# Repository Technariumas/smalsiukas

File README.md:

# smalsiukas
The conversion of a forklift trucks to a line following robot. 

A file set related to conversion of BT C3E C4E forklift truck and Linde lifter to a line-following robot for an art installation of [Robertas Narkus "Träger"](http://cac.lt/en/exhibitions/future/8547)

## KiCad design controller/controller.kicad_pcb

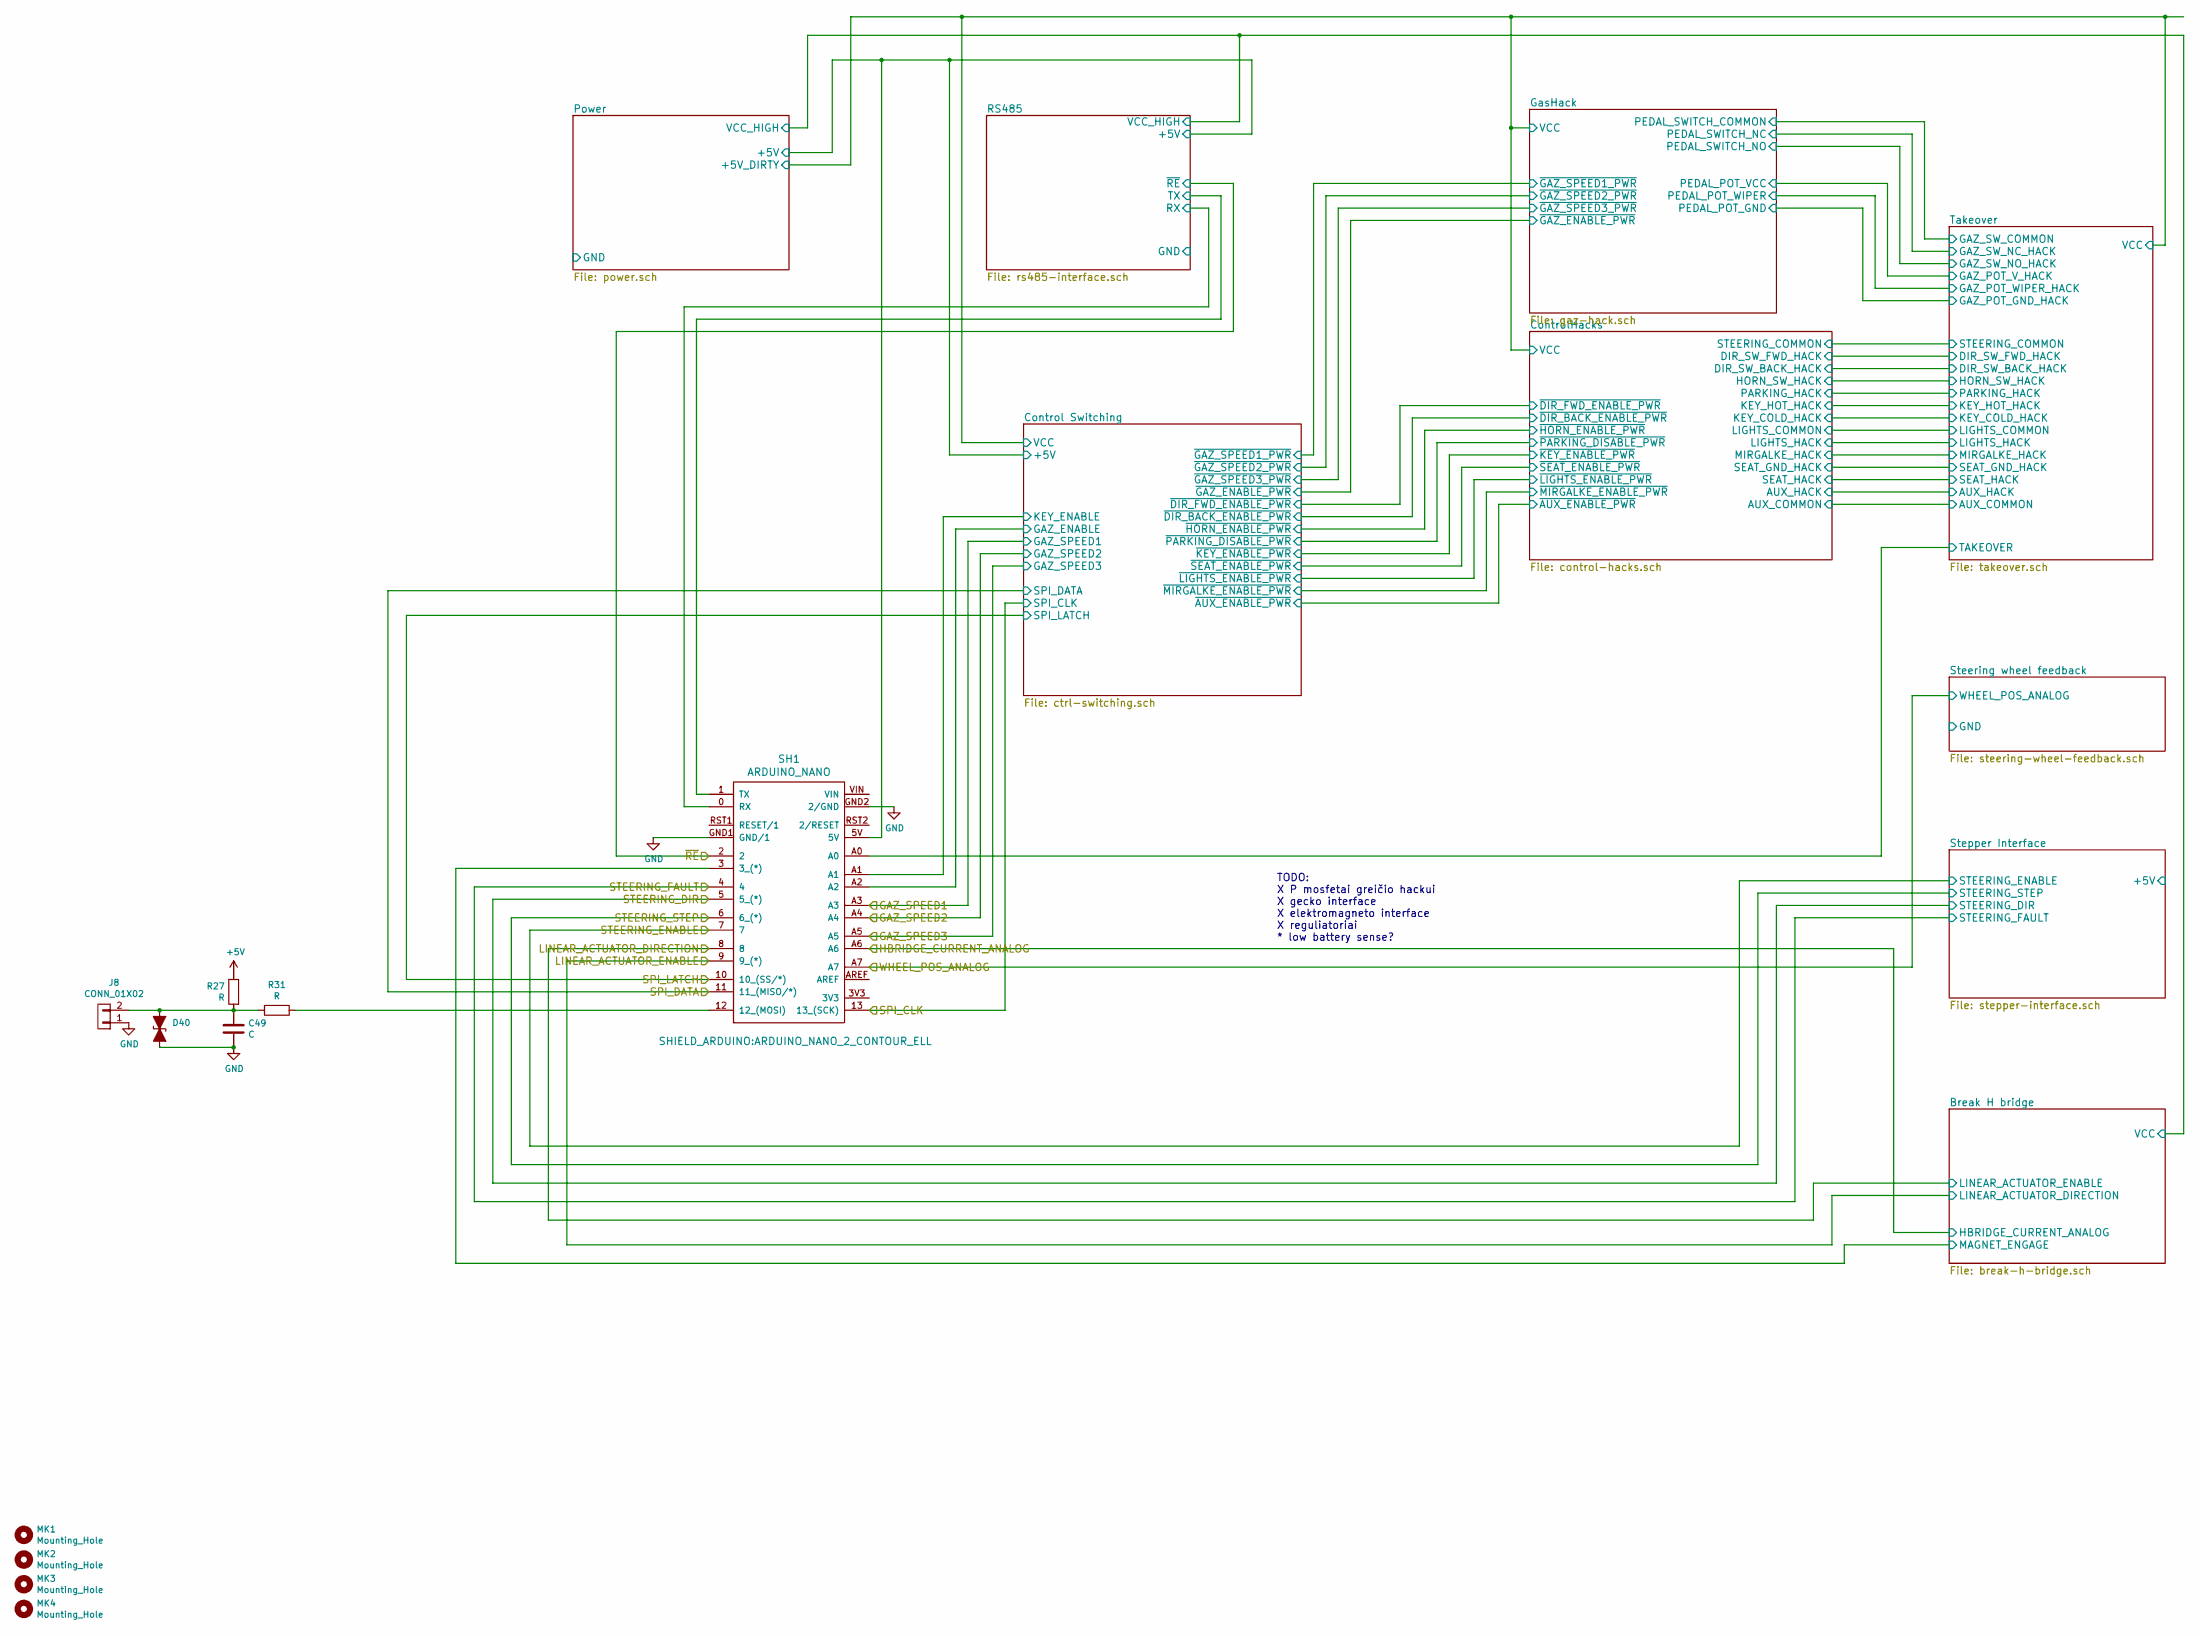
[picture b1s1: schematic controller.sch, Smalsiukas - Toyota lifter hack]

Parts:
C49: C; C_0603_HandSoldering; PartNo ?
D40: D_TVS_ALT; SOD-323; PartNo ?
J8: CONN_01X02; JST_EH_B02B-EH-A_02x2.50mm_Straight; PartNo ?
MK1, MK2, MK3, MK4: Mounting_Hole; MountingHole_3.2mm_M3; PartNo ?
R27, R31: R; R_0603_HandSoldering; PartNo ?
SH1: ARDUINO_NANO; ARDUINO_NANO_2_CONTOUR_ELL; PartNo ?

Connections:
+5V: R27.1, SH1.5V; also elsewhere on the board
/Break H bridge/MAGNET_ENGAGE: SH1.3 (3_(*)); also elsewhere on the board
/Control Switching/GAZ_ENABLE: SH1.A2; also elsewhere on the board
/Control Switching/KEY_ENABLE: SH1.A1; also elsewhere on the board
/GAZ_SPEED1: SH1.A3; also elsewhere on the board
/GAZ_SPEED2: SH1.A4; also elsewhere on the board
/GAZ_SPEED3: SH1.A5; also elsewhere on the board
/HBRIDGE_CURRENT_ANALOG: SH1.A6; also elsewhere on the board
/LINEAR_ACTUATOR_DIRECTION: SH1.8; also elsewhere on the board
/LINEAR_ACTUATOR_ENABLE: SH1.9 (9_(*)); also elsewhere on the board
/RS485/RX: SH1.0 (RX); also elsewhere on the board
/RS485/TX: SH1.1 (TX); also elsewhere on the board
/SPI_CLK: SH1.13 (13_(SCK)); also elsewhere on the board
/SPI_DATA: SH1.11 (11_(MISO/*)); also elsewhere on the board
/SPI_LATCH: SH1.10 (10_(SS/*)); also elsewhere on the board
/STEERING_DIR: SH1.5 (5_(*)); also elsewhere on the board
/STEERING_ENABLE: SH1.7; also elsewhere on the board
/STEERING_FAULT: SH1.4; also elsewhere on the board
/STEERING_STEP: SH1.6 (6_(*)); also elsewhere on the board
/Takeover/TAKEOVER: SH1.A0; also elsewhere on the board
/WHEEL_POS_ANALOG: SH1.A7; also elsewhere on the board
/~RE: SH1.2; also elsewhere on the board
GND: C49.2, D40.2 (A2), J8.1, SH1.GND1 (GND/1), SH1.GND2 (2/GND); also elsewhere on the board
unnamed: C49.1, D40.1 (A1), J8.2, R27.2, R31.2
unnamed: R31.1, SH1.12 (12_(MOSI))

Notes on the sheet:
TODO: X P mosfetai greičio hackui X gecko interface X elektromagneto interface X reguliatoriai * low battery sense?

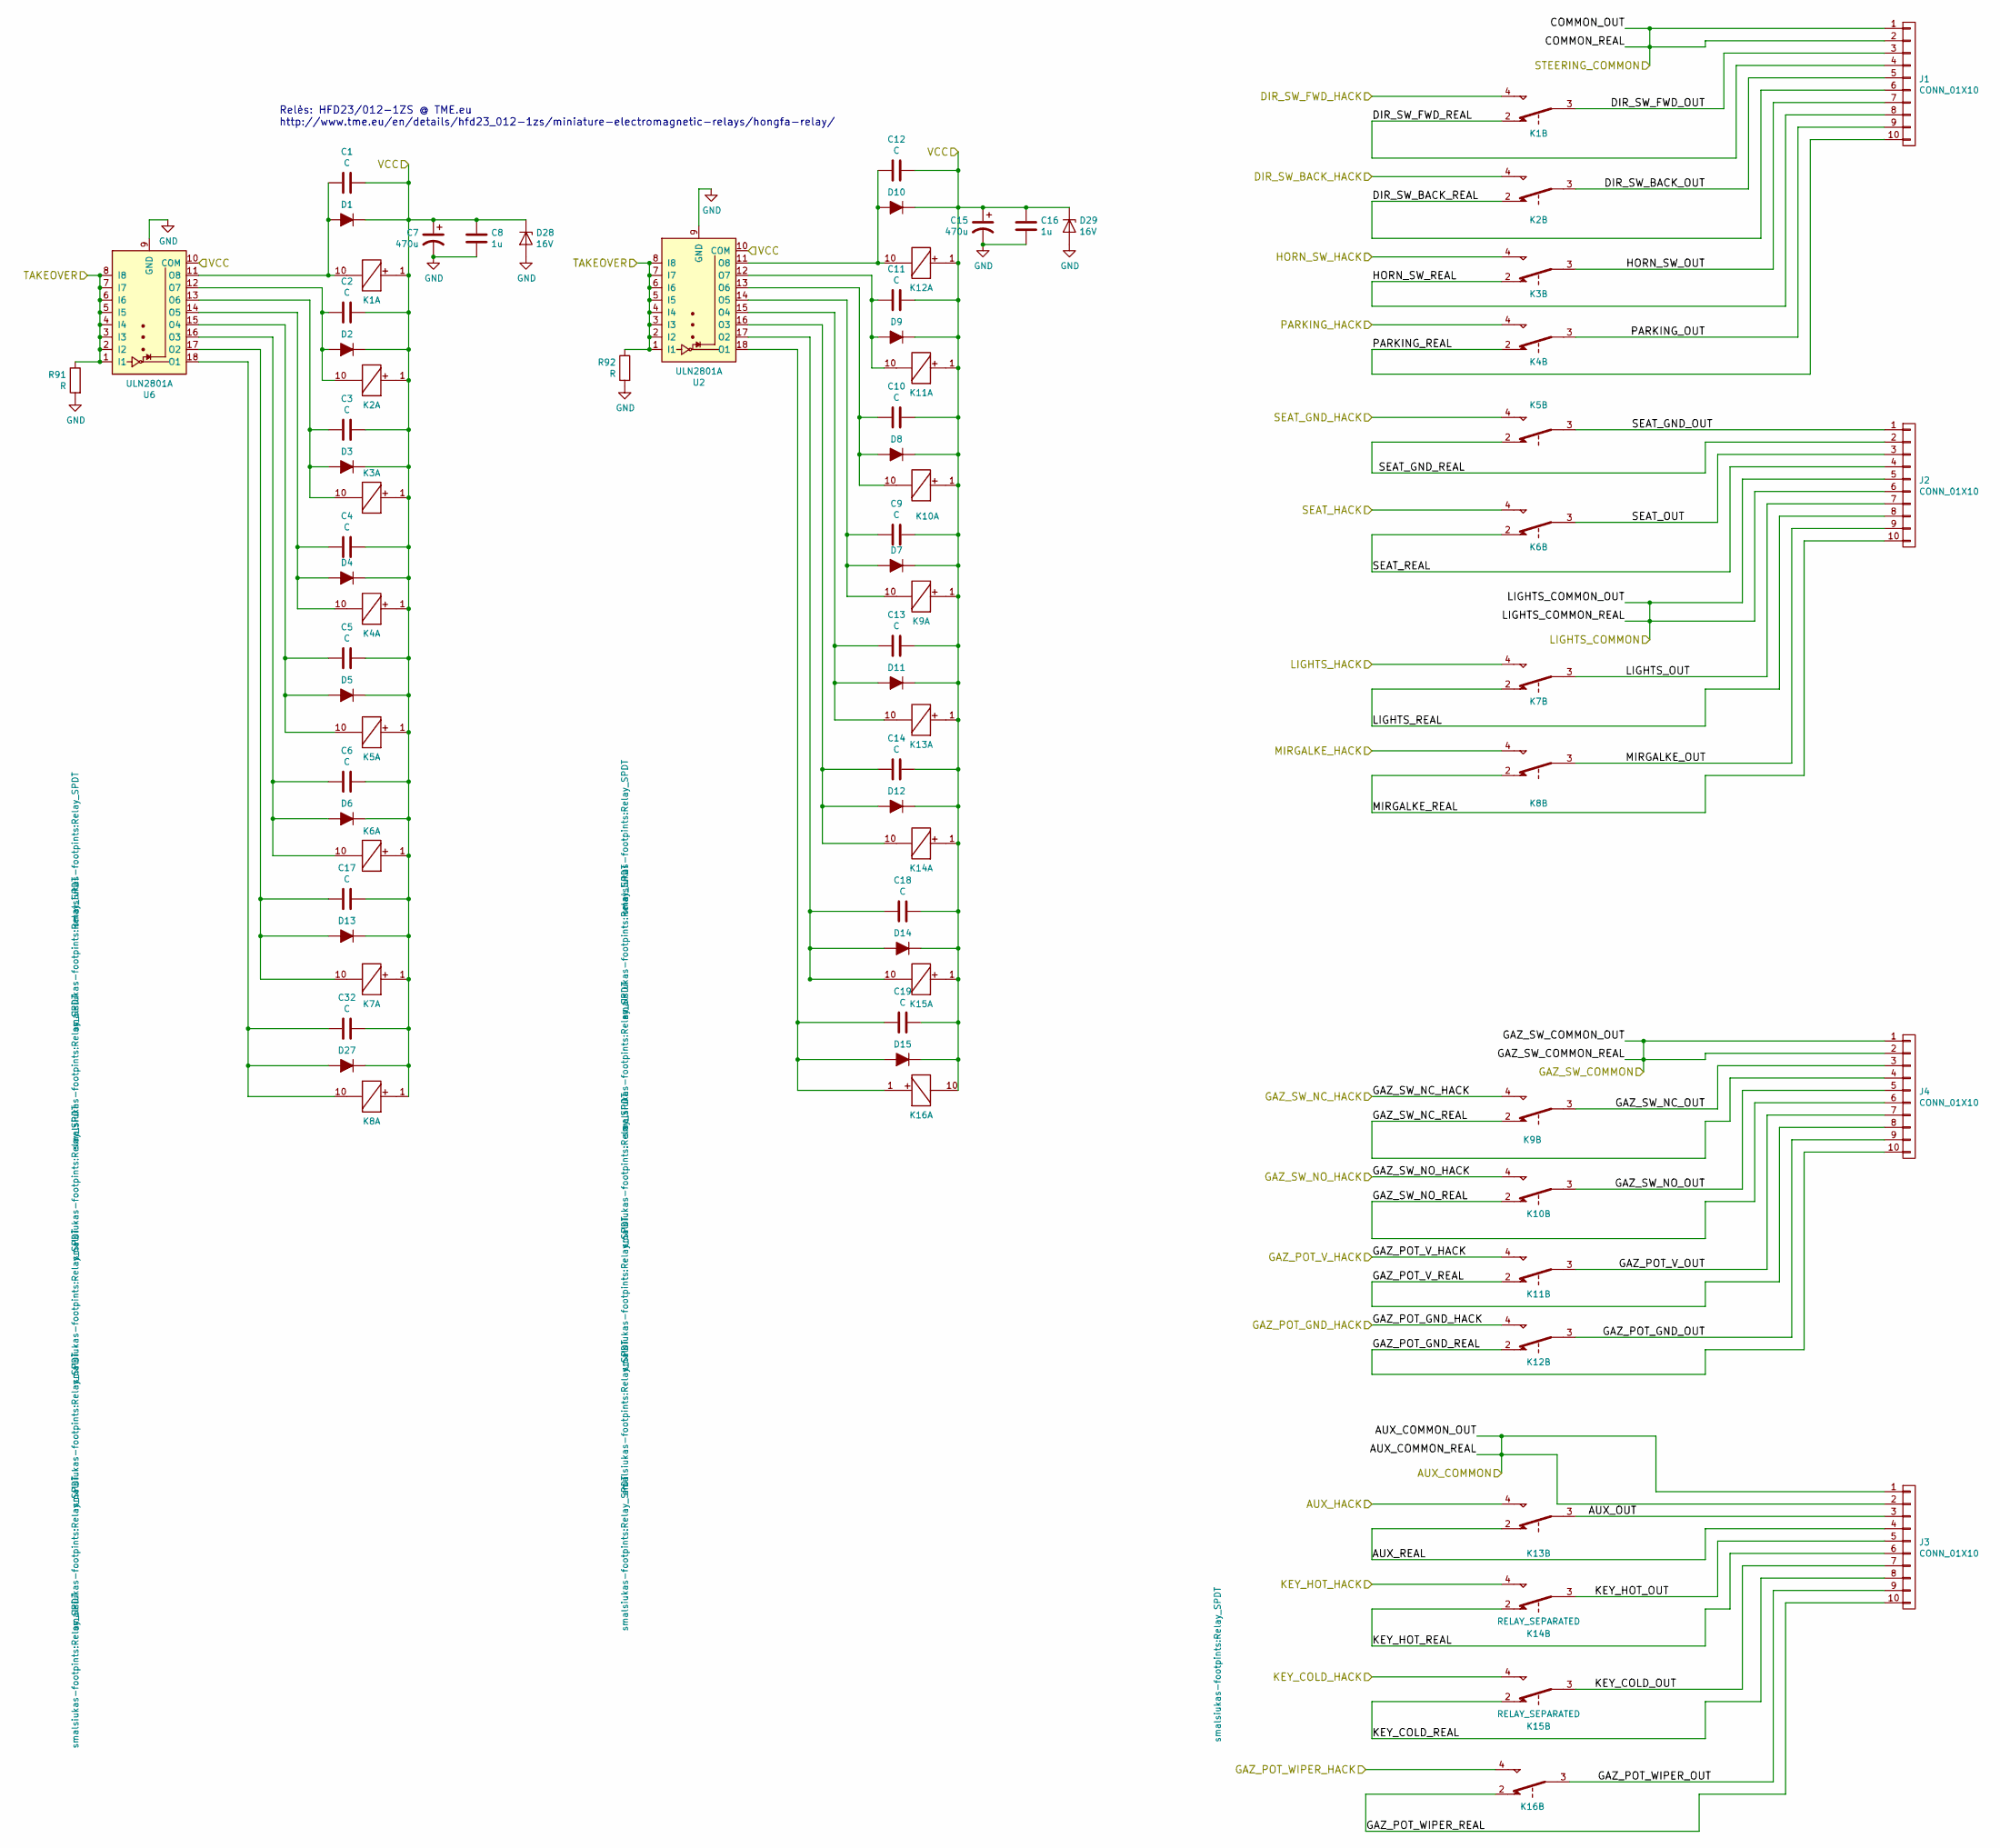
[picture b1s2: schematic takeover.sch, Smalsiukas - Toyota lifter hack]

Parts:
C1, C2, C3, C4, C5, C6, C9, C10, C11, C12, C13, C14, C17, C18, C19, C32: C; C_0603_HandSoldering; PartNo ?
C7, C15: 470u; CP_Radial_D16.0mm_P7.50mm; PartNo ECA2AAM471X
C8, C16: 1u; C_1210_HandSoldering; PartNo ?
D1: D_ALT; D_SOD-123; PartNo PMEG2020EH
D2, D3, D4, D5, D6, D7, D8, D9, D10, D11, D12, D13, D14, D15, D27: D_ALT; D_SOD-123; PartNo ?
D28, D29: 16V; D_SMB_Handsoldering; PartNo 1SMB5930BT3G
J1, J2, J3, J4: CONN_01X10; TerminalBlock_5.08-10pol; PartNo 21.95MH/10-E
K1, K2, K3, K4, K5, K6, K7, K8, K9, K10, K11, K12, K13, K14, K15, K16: RELAY_SEPARATED; Relay_SPDT; PartNo ?
R91, R92: R; R_0603_HandSoldering
U2, U6: ULN2801A; SOIC-18W_7.5x11.6mm_Pitch1.27mm; PartNo ULN2803ADWR

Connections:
/ControlHacks/AUX_COMMON: J3.1, J3.2; also elsewhere on the board
/ControlHacks/AUX_HACK: K13.4; also elsewhere on the board
/ControlHacks/DIR_SW_BACK_HACK: K2.4; also elsewhere on the board
/ControlHacks/DIR_SW_FWD_HACK: K1.4; also elsewhere on the board
/ControlHacks/HORN_SW_HACK: K3.4; also elsewhere on the board
/ControlHacks/KEY_COLD_HACK: K15.4; also elsewhere on the board
/ControlHacks/KEY_HOT_HACK: K14.4; also elsewhere on the board
/ControlHacks/LIGHTS_COMMON: J2.5, J2.6; also elsewhere on the board
/ControlHacks/LIGHTS_HACK: K7.4; also elsewhere on the board
/ControlHacks/MIRGALKE_HACK: K8.4; also elsewhere on the board
/ControlHacks/PARKING_HACK: K4.4; also elsewhere on the board
/ControlHacks/SEAT_GND_HACK: K5.4; also elsewhere on the board
/ControlHacks/SEAT_HACK: K6.4; also elsewhere on the board
/ControlHacks/STEERING_COMMON: J1.1, J1.2; also elsewhere on the board
/Power/+5V_DIRTY: C1.1, C2.1, C3.1, C4.1, C5.1, C6.1, C7.1, C8.2, C9.1, C10.1, C11.1, C12.1, C13.1, C14.1, C15.1, C16.2, C17.1, C18.1, C19.1, C32.1, D1.1 (K), D2.1 (K), D3.1 (K), D4.1 (K), D5.1 (K), D6.1 (K), D7.1 (K), D8.1 (K), D9.1 (K), D10.1 (K), D11.1 (K), D12.1 (K), D13.1 (K), D14.1 (K), D15.1 (K), D27.1 (K), D28.1 (K), D29.1 (K), K1.1, K2.1, K3.1, K4.1, K5.1, K6.1, K7.1, K8.1, K9.1, K10.1, K11.1, K12.1, K13.1, K14.1, K15.1, K16.10, U2.10 (COM), U6.10 (COM); also elsewhere on the board
/Takeover/AUX_OUT: J3.3, K13.3
/Takeover/AUX_REAL: J3.4, K13.2
/Takeover/DIR_SW_BACK_OUT: J1.5, K2.3
/Takeover/DIR_SW_BACK_REAL: J1.6, K2.2
/Takeover/DIR_SW_FWD_OUT: J1.3, K1.3
/Takeover/DIR_SW_FWD_REAL: J1.4, K1.2
/Takeover/GAZ_POT_GND_HACK: K12.4; also elsewhere on the board
/Takeover/GAZ_POT_GND_OUT: J4.9, K12.3
/Takeover/GAZ_POT_GND_REAL: J4.10, K12.2
/Takeover/GAZ_POT_V_HACK: K11.4; also elsewhere on the board
/Takeover/GAZ_POT_V_OUT: J4.7, K11.3
/Takeover/GAZ_POT_V_REAL: J4.8, K11.2
/Takeover/GAZ_POT_WIPER_HACK: K16.4; also elsewhere on the board
/Takeover/GAZ_POT_WIPER_OUT: J3.9, K16.3
/Takeover/GAZ_POT_WIPER_REAL: J3.10, K16.2
/Takeover/GAZ_SW_COMMON: J4.1, J4.2; also elsewhere on the board
/Takeover/GAZ_SW_NC_HACK: K9.4; also elsewhere on the board
/Takeover/GAZ_SW_NC_OUT: J4.3, K9.3
/Takeover/GAZ_SW_NC_REAL: J4.4, K9.2
/Takeover/GAZ_SW_NO_HACK: K10.4; also elsewhere on the board
/Takeover/GAZ_SW_NO_OUT: J4.5, K10.3
/Takeover/GAZ_SW_NO_REAL: J4.6, K10.2
/Takeover/HORN_SW_OUT: J1.7, K3.3
/Takeover/HORN_SW_REAL: J1.8, K3.2
/Takeover/KEY_COLD_OUT: J3.7, K15.3
/Takeover/KEY_COLD_REAL: J3.8, K15.2
/Takeover/KEY_HOT_OUT: J3.5, K14.3
/Takeover/KEY_HOT_REAL: J3.6, K14.2
/Takeover/LIGHTS_OUT: J2.7, K7.3
/Takeover/LIGHTS_REAL: J2.8, K7.2
/Takeover/MIRGALKE_OUT: J2.9, K8.3
/Takeover/MIRGALKE_REAL: J2.10, K8.2
/Takeover/PARKING_OUT: J1.9, K4.3
/Takeover/PARKING_REAL: J1.10, K4.2
/Takeover/SEAT_GND_OUT: J2.1, K5.3
/Takeover/SEAT_GND_REAL: J2.2, K5.2
/Takeover/SEAT_OUT: J2.3, K6.3
/Takeover/SEAT_REAL: J2.4, K6.2
/Takeover/TAKEOVER: R91.1, R92.1, U2.1 (I1), U2.2 (I2), U2.3 (I3), U2.4 (I4), U2.5 (I5), U2.6 (I6), U2.7 (I7), U2.8 (I8), U6.1 (I1), U6.2 (I2), U6.3 (I3), U6.4 (I4), U6.5 (I5), U6.6 (I6), U6.7 (I7), U6.8 (I8); also elsewhere on the board
GND: C7.2, C8.1, C15.2, C16.1, D28.2 (A), D29.2 (A), R91.2, R92.2, U2.9 (GND), U6.9 (GND); also elsewhere on the board
unnamed: C1.2, D1.2 (A), K1.10, U6.11 (O8)
unnamed: C2.2, D2.2 (A), K2.10, U6.12 (O7)
unnamed: C3.2, D3.2 (A), K3.10, U6.13 (O6)
unnamed: C4.2, D4.2 (A), K4.10, U6.14 (O5)
unnamed: C5.2, D5.2 (A), K5.10, U6.15 (O4)
unnamed: C6.2, D6.2 (A), K6.10, U6.16 (O3)
unnamed: C9.2, D7.2 (A), K9.10, U2.14 (O5)
unnamed: C10.2, D8.2 (A), K10.10, U2.13 (O6)
unnamed: C11.2, D9.2 (A), K11.10, U2.12 (O7)
unnamed: C12.2, D10.2 (A), K12.10, U2.11 (O8)
unnamed: C13.2, D11.2 (A), K13.10, U2.15 (O4)
unnamed: C14.2, D12.2 (A), K14.10, U2.16 (O3)
unnamed: C17.2, D13.2 (A), K7.10, U6.17 (O2)
unnamed: C18.2, D14.2 (A), K15.10, U2.17 (O2)
unnamed: C19.2, D15.2 (A), K16.1, U2.18 (O1)
unnamed: C32.2, D27.2 (A), K8.10, U6.18 (O1)

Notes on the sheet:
Relės: HFD23/012-1ZS @ TME.eu http://www.tme.eu/en/details/hfd23_012-1zs/miniature-electromagnetic-relays/hongfa-relay/

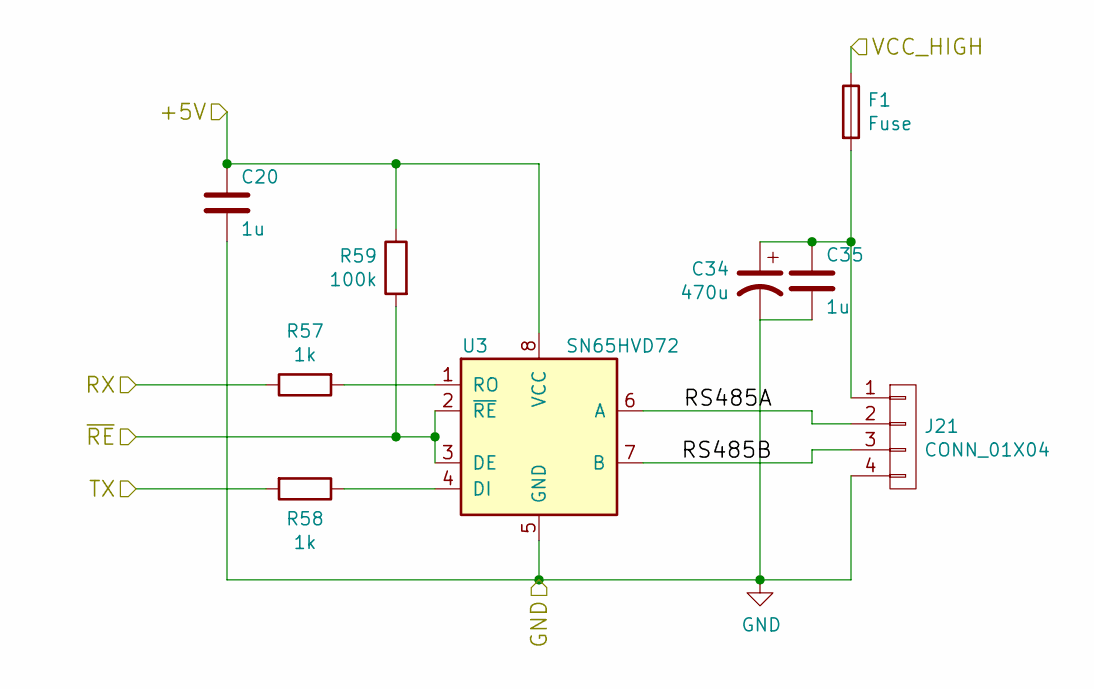
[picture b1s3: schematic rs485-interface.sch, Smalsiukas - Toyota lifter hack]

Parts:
C20, C35: 1u; C_0603_HandSoldering
C34: 470u; CP_Radial_D16.0mm_P7.50mm; PartNo ECA2AAM471X
F1: Fuse; Automotive-Fuse-Holder; PartNo ?
J21: CONN_01X04; JST_EH_B04B-EH-A_04x2.50mm_Straight; PartNo ?
R57, R58: 1k; R_0603_HandSoldering
R59: 100k; R_0603_HandSoldering
U3: SN65HVD72; SOIC-8_3.9x4.9mm_Pitch1.27mm; PartNo MAX13442EASA

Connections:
+5V: C20.1, R59.1, U3.8 (VCC); also elsewhere on the board
/RS485/RS485A: J21.2, U3.6 (A)
/RS485/RS485B: J21.3, U3.7 (B)
/RS485/RX: R57.1; also elsewhere on the board
/RS485/TX: R58.2; also elsewhere on the board
/~RE: R59.2, U3.2 (~RE~), U3.3 (DE); also elsewhere on the board
GND: C20.2, C34.2, C35.2, J21.4, U3.5 (GND); also elsewhere on the board
unnamed: C34.1, C35.1, F1.2, J21.1
unnamed: R57.2, U3.1 (RO)
unnamed: R58.1, U3.4 (DI)
VCC: F1.1; also elsewhere on the board

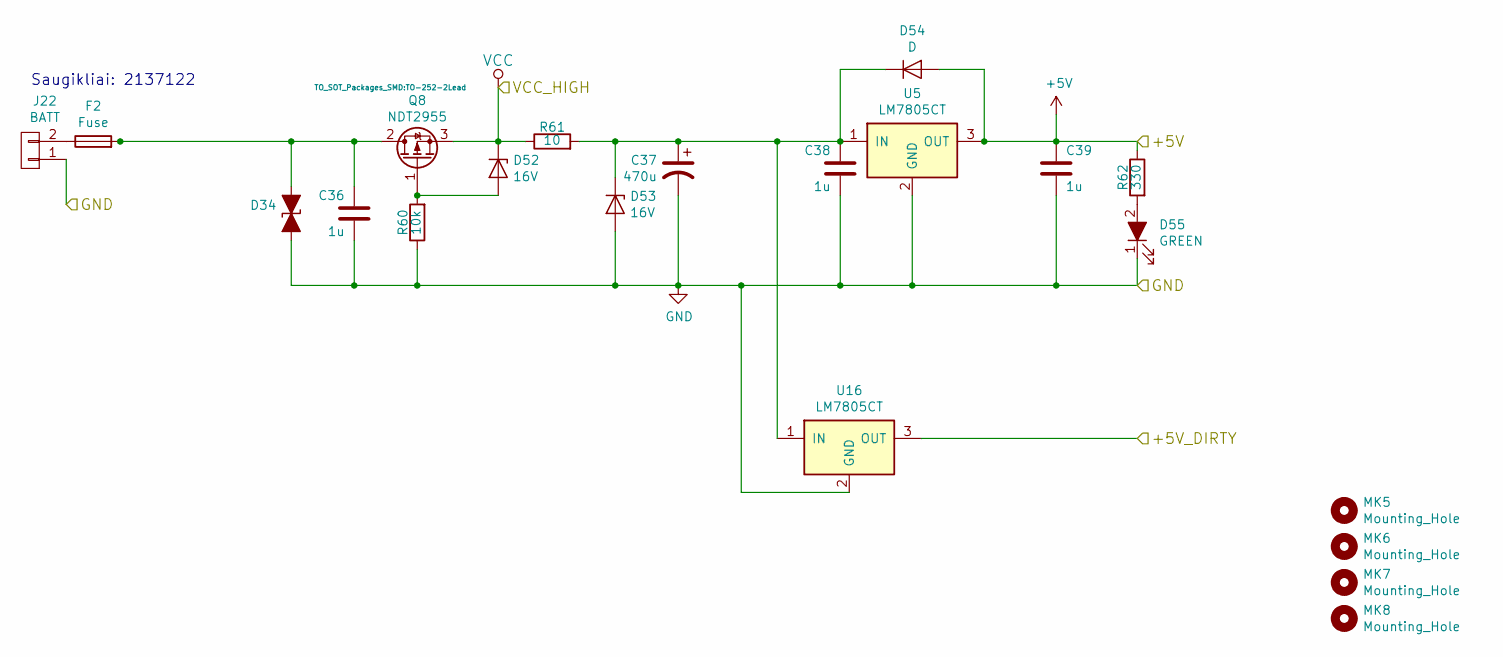
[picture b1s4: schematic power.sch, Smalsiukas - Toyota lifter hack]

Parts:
C36, C38: 1u; C_1210_HandSoldering; PartNo ?
C37: 470u; CP_Radial_D16.0mm_P7.50mm; PartNo ECA2AAM471X
C39: 1u; C_0603
D34: D_TVS_ALT; Diode-SMC_Handsoldering; PartNo ?
D52, D53: 16V; D_SMB_Handsoldering; PartNo 1SMB5930BT3G
D54: D; D_SOD-123; PartNo ?
D55: GREEN; LED_D5.0mm; PartNo ?
F2: Fuse; Automotive-Fuse-Holder; PartNo ?
J22: BATT; TerminalBlock_5.08-2pol; PartNo ?
MK5, MK6, MK7, MK8: Mounting_Hole; MountingHole_3.2mm_M3; PartNo ?
Q8: NDT2955; TO-252-2Lead; PartNo IRFR5410TRPBF
R60: 10k; R_0603_HandSoldering; PartNo ?
R61: 10; R_0805_HandSoldering; PartNo ?
R62: 330; R_0603
U5: LM7805CT; TO-252-2Lead; PartNo KA7805ERTF
U16: LM7805CT; TO-220_Vertical; PartNo OKI-78SR-5/1.5-W36-C

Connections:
+5V: C39.1, D54.2 (A), R62.1, U5.3 (OUT); also elsewhere on the board
/Power/+5V_DIRTY: U16.3 (OUT); also elsewhere on the board
GND: C36.2, C37.2, C38.2, C39.2, D34.2 (A2), D53.2 (A), D55.1 (K), J22.1, R60.1, U5.2 (GND), U16.2 (GND); also elsewhere on the board
unnamed: C36.1, D34.1 (A1), F2.2, Q8.2 (D)
unnamed: C37.1, C38.1, D53.1 (K), D54.1 (K), R61.2, U5.1 (IN), U16.1 (IN)
unnamed: D52.2 (A), Q8.1 (G), R60.2
unnamed: D55.2 (A), R62.2
unnamed: F2.1, J22.2
VCC: D52.1 (K), Q8.3 (S), R61.1; also elsewhere on the board

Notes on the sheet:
Saugikliai: 2137122

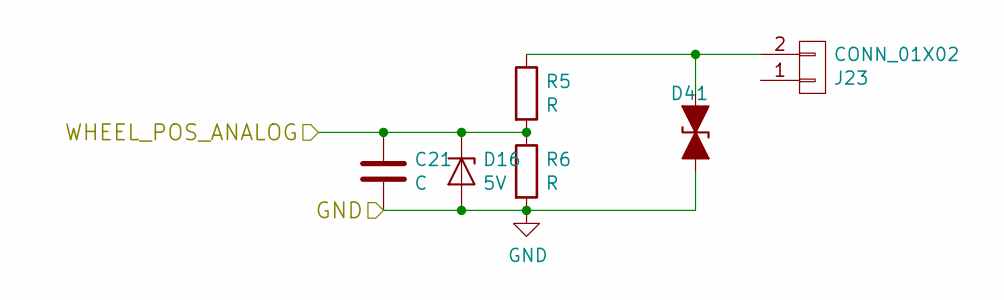
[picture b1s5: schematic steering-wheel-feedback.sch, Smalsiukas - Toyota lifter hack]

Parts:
C21: C; C_0603_HandSoldering
D16: 5V; SOD-123; PartNo ?
D41: D_TVS_ALT; SOD-323; PartNo ?
J23: CONN_01X02; TerminalBlock_5.08-2pol; PartNo ?
R5, R6: R; R_0603_HandSoldering

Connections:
/WHEEL_POS_ANALOG: C21.1, D16.1 (K), R5.2, R6.1; also elsewhere on the board
GND: C21.2, D16.2 (A), D41.2 (A2), R6.2; also elsewhere on the board
unnamed: D41.1 (A1), J23.2, R5.1

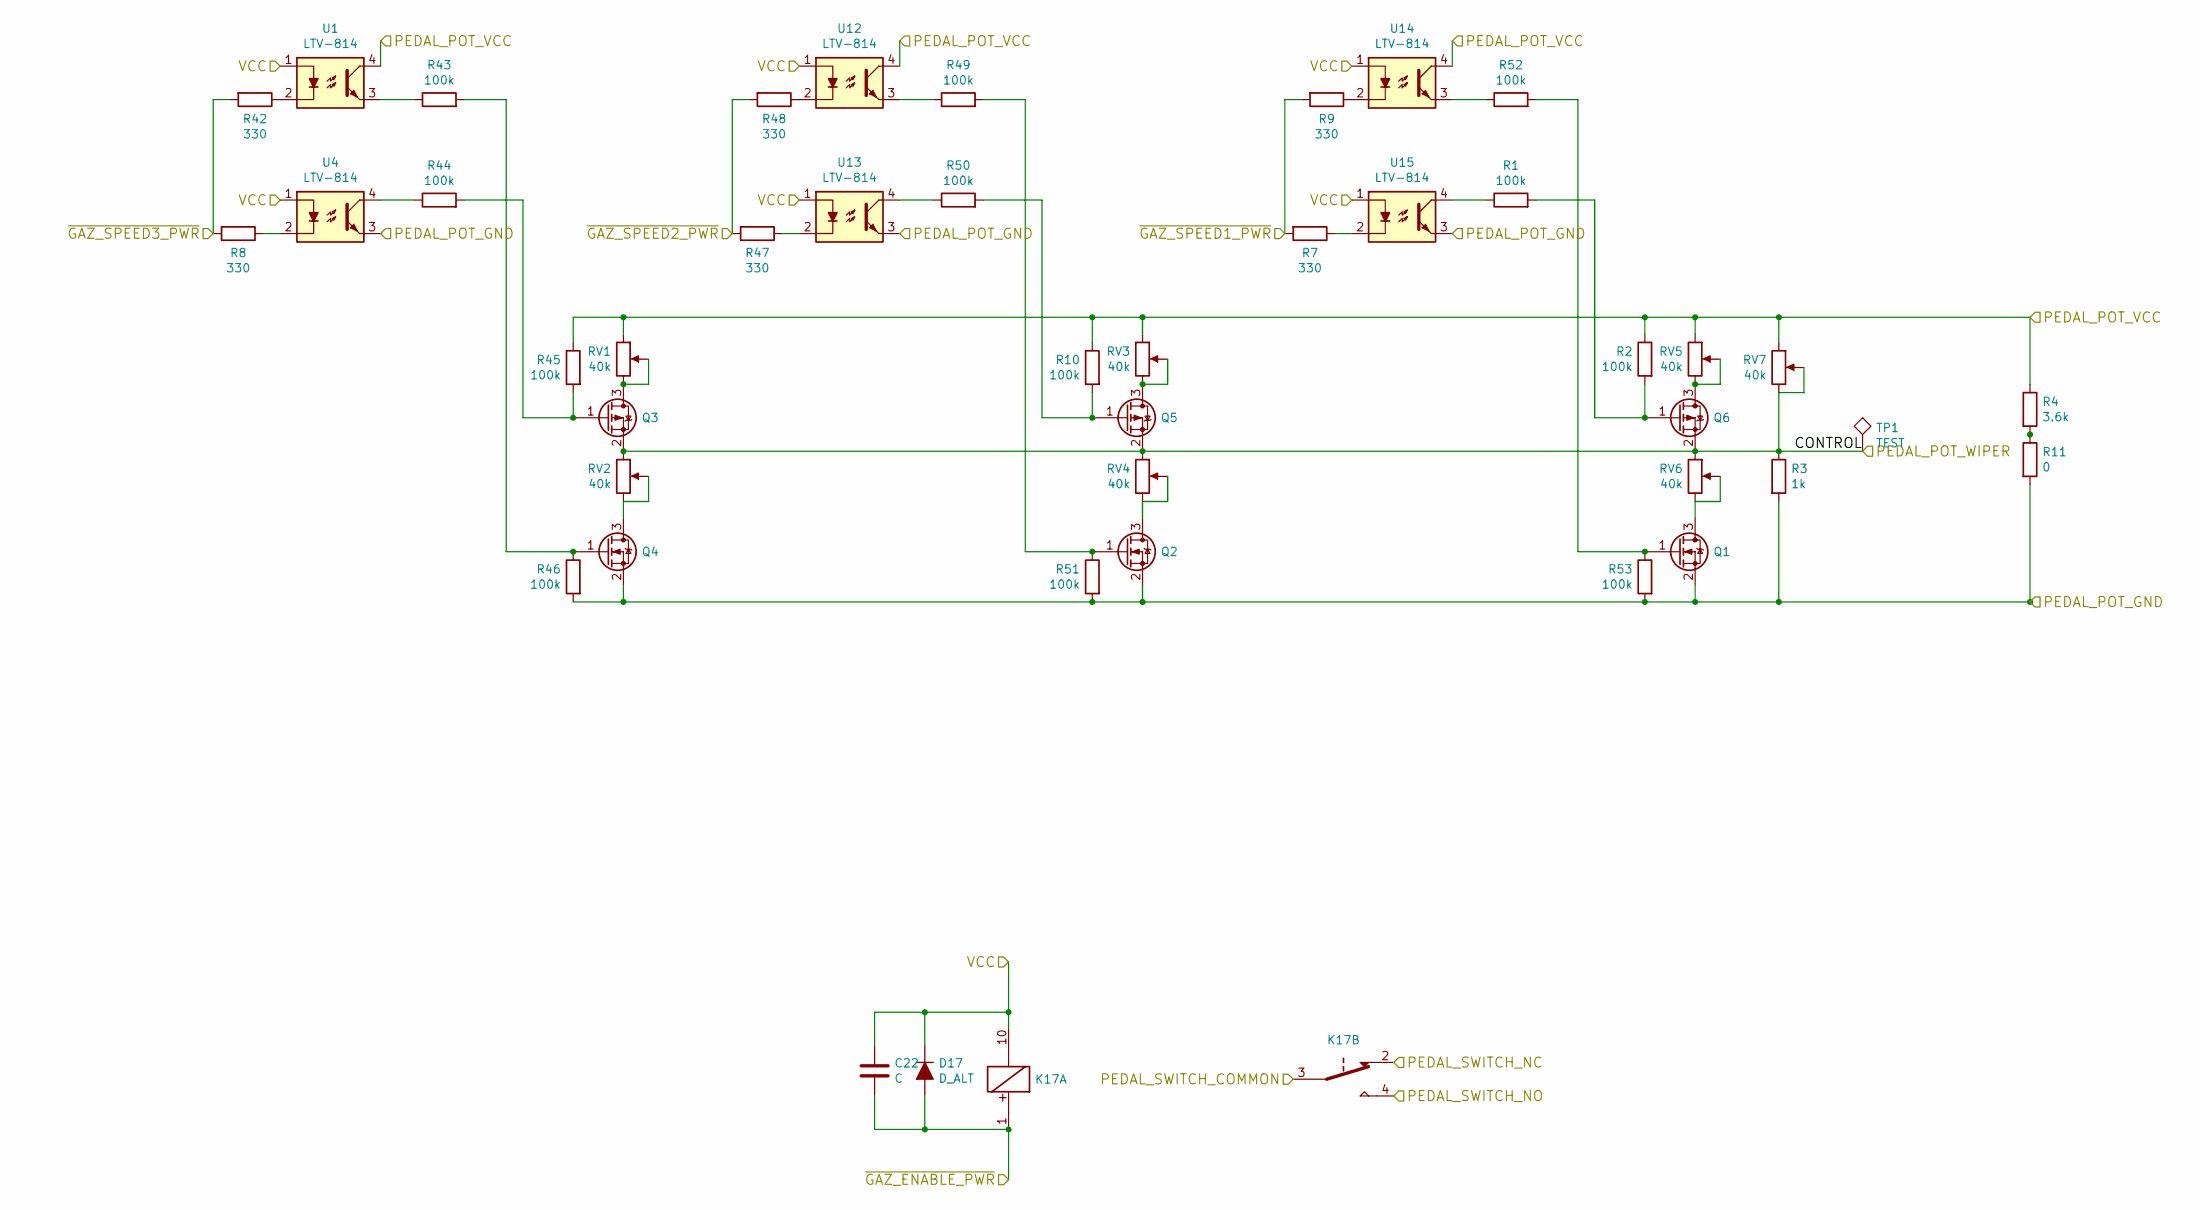
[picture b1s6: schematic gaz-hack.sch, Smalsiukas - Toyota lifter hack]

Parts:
C22: C; C_0603_HandSoldering
D17: D_ALT; D_SOD-123
K17: RELAY_SEPARATED; Relay_SPDT
Q1, Q2, Q4: Q_NMOS_GSD; SOT-23_Handsoldering; PartNo ?
Q3, Q5, Q6: Q_PMOS_GSD; SOT-23_Handsoldering; PartNo ?
R1, R2, R10, R43, R44, R45, R46, R49, R50, R51, R52, R53: 100k; R_0603_HandSoldering
R3: 1k; R_0603_HandSoldering
R4: 3.6k; R_0603_HandSoldering
R7, R8, R9, R42, R47, R48: 330; R_0603_HandSoldering
R11: 0; R_0603_HandSoldering
RV1, RV2, RV3, RV4, RV5, RV6, RV7: 40k; Potentiometer_Trimmer_Bourns_3296W; PartNo ?
TP1: TEST; Measurement_Point_Round-TH_Small; PartNo ?
U1, U4, U12, U13, U14, U15: LTV-814; DIP-4_W11.48mm_SMD; PartNo ?

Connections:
/Control Switching/~GAZ_ENABLE_PWR: C22.2, D17.2 (A), K17.1; also elsewhere on the board
/Control Switching/~GAZ_SPEED1_PWR: R7.2, R9.2; also elsewhere on the board
/Control Switching/~GAZ_SPEED2_PWR: R47.2, R48.2; also elsewhere on the board
/Control Switching/~GAZ_SPEED3_PWR: R8.2, R42.2; also elsewhere on the board
/Power/+5V_DIRTY: C22.1, D17.1 (K), K17.10, U1.1, U4.1, U12.1, U13.1, U14.1, U15.1; also elsewhere on the board
/Takeover/GAZ_POT_GND_HACK: Q1.2 (S), Q2.2 (S), Q4.2 (S), R3.2, R11.2, R46.2, R51.2, R53.2, U4.3, U13.3, U15.3; also elsewhere on the board
/Takeover/GAZ_POT_V_HACK: R2.1, R4.1, R10.1, R45.1, RV1.1, RV3.1, RV5.1, RV7.1, U1.4, U12.4, U14.4; also elsewhere on the board
/Takeover/GAZ_POT_WIPER_HACK: Q3.2 (S), Q5.2 (S), Q6.2 (S), R3.1, RV2.1, RV4.1, RV6.1, RV7.2, RV7.3, TP1.1; also elsewhere on the board
/Takeover/GAZ_SW_COMMON: K17.3; also elsewhere on the board
/Takeover/GAZ_SW_NC_HACK: K17.2; also elsewhere on the board
/Takeover/GAZ_SW_NO_HACK: K17.4; also elsewhere on the board
unnamed: Q1.1 (G), R52.2, R53.1
unnamed: Q1.3 (D), RV6.2, RV6.3
unnamed: Q2.1 (G), R49.2, R51.1
unnamed: Q2.3 (D), RV4.2, RV4.3
unnamed: Q3.1 (G), R44.2, R45.2
unnamed: Q3.3 (D), RV1.2, RV1.3
unnamed: Q4.1 (G), R43.2, R46.1
unnamed: Q4.3 (D), RV2.2, RV2.3
unnamed: Q5.1 (G), R10.2, R50.2
unnamed: Q5.3 (D), RV3.2, RV3.3
unnamed: Q6.1 (G), R1.2, R2.2
unnamed: Q6.3 (D), RV5.2, RV5.3
unnamed: R1.1, U15.4
unnamed: R7.1, U15.2
unnamed: R8.1, U4.2
unnamed: R9.1, U14.2
unnamed: R4.2, R11.1
unnamed: R42.1, U1.2
unnamed: R43.1, U1.3
unnamed: R44.1, U4.4
unnamed: R47.1, U13.2
unnamed: R48.1, U12.2
unnamed: R49.1, U12.3
unnamed: R50.1, U13.4
unnamed: R52.1, U14.3

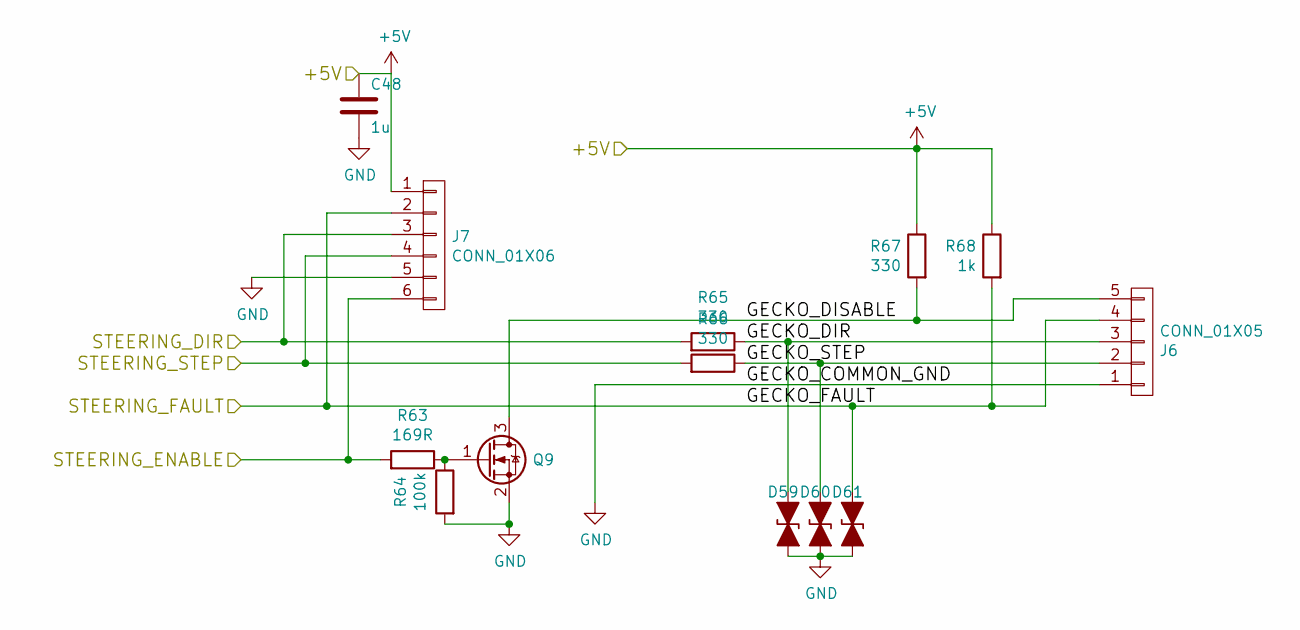
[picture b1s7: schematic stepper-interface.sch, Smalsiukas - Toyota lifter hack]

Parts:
C48: 1u; C_0603
D59, D60, D61: D_TVS_ALT; SOD-323; PartNo ?
J6: CONN_01X05; TerminalBlock_5.08-5pol; PartNo ?
J7: CONN_01X06; Socket_Strip_Straight_1x06_Pitch2.54mm; PartNo ?
Q9: Q_NMOS_GSD; SOT-23_Handsoldering
R63: 169R; R_0603_HandSoldering; PartNo ?
R64: 100k; R_0603_HandSoldering; PartNo ?
R65, R66, R67: 330; R_0603_HandSoldering; PartNo ?
R68: 1k; R_0603_HandSoldering; PartNo ?

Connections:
+5V: C48.1, J7.1, R67.1, R68.1; also elsewhere on the board
/STEERING_DIR: J7.3, R65.2; also elsewhere on the board
/STEERING_ENABLE: J7.6, R63.2; also elsewhere on the board
/STEERING_FAULT: D61.1 (A1), J6.4, J7.2, R68.2; also elsewhere on the board
/STEERING_STEP: J7.4, R66.2; also elsewhere on the board
/Stepper Interface/GECKO_DIR: D59.1 (A1), J6.3, R65.1
/Stepper Interface/GECKO_DISABLE: J6.5, Q9.3 (D), R67.2
/Stepper Interface/GECKO_STEP: D60.1 (A1), J6.2, R66.1
GND: C48.2, D59.2 (A2), D60.2 (A2), D61.2 (A2), J6.1, J7.5, Q9.2 (S), R64.2; also elsewhere on the board
unnamed: Q9.1 (G), R63.1, R64.1
